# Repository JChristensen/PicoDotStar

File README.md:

# Pico DotStar Driver  
https://github.com/JChristensen/PicoDotstar  
README file  
Jack Christensen  
Apr-2025

## License
  
This work is licensed under the [Creative Commons Attribution-ShareAlike 4.0 International License](https://creativecommons.org/licenses/by-sa/4.0/).

## Overview
This is just a simple carrier board for a Raspberry Pi Pico and an RTC as I begin working with the Pico. I have a couple old projects that use AVR MCUs to drive DotStar LEDs, so replacing those with Picos sounded fairly straightforward. I added a button, three LEDs, and another header with some GPIO pins, so I may also use the board for general experimentation. Once I figure out the Pico's RTC, a separate RTC may not be needed.

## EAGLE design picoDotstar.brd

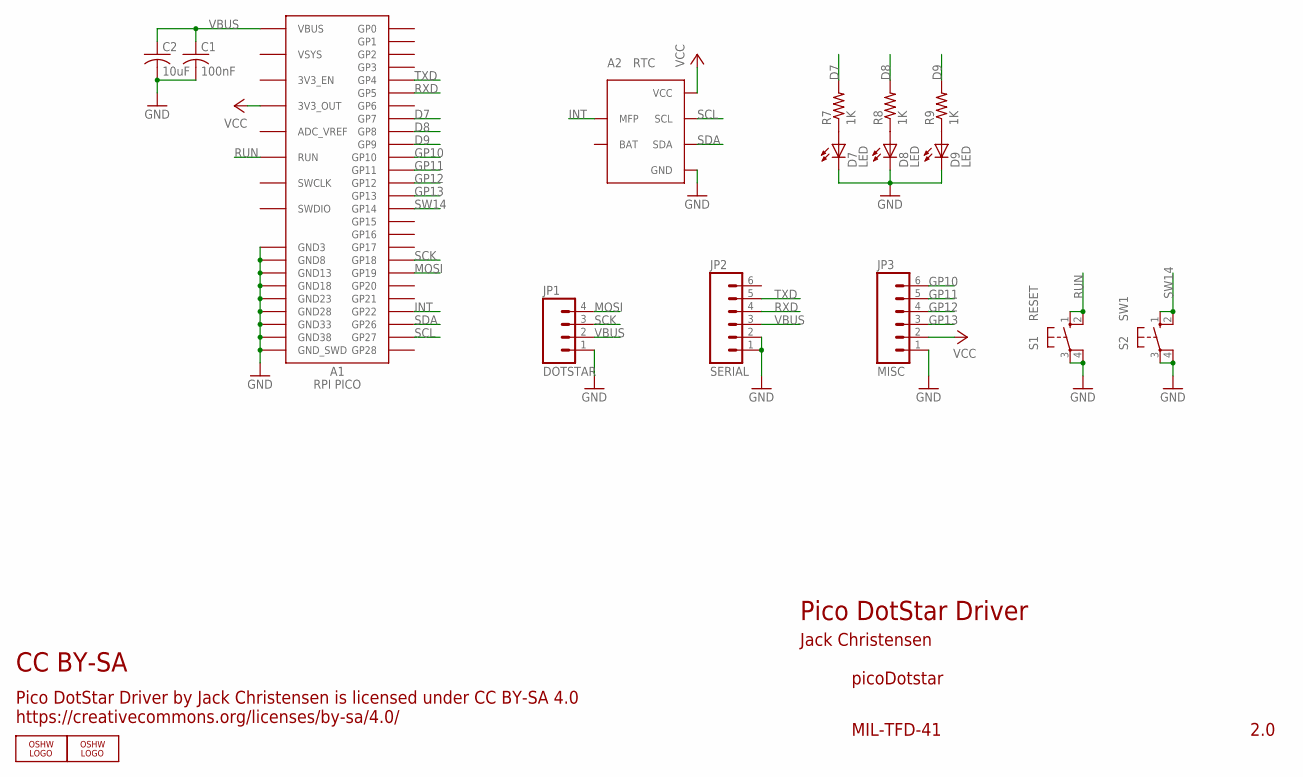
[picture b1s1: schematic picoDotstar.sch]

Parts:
A1: RPI PICO; PICO
A2: RTC; RTC79412
C1: 100nF; M0805
C2: 10uF; M0805
D7, D8, D9: LED; D0805
JP1: DOTSTAR; 1X04_LOCK
JP2: SERIAL; 1X06_LOCK
JP3: MISC; 1X06_LOCK
LOGO2: OSHW_LOGO_8MILX0100-NT; OSHW_8X100_NOTEXT
LOGO3: OSHW_LOGO_8MILX0150-NT; OSHW_8X150_NOTEXT
R7, R8, R9: 1K; M0805
S1: RESET; B3F-10XXOCT
S2: SW1; B3F-10XXOCT

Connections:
D7: A1.P$10 (GP7), R7.2
D8: A1.P$11 (GP8), R8.2
D9: A1.P$12 (GP9), R9.2
GND: A1.P$03 (GND3), A1.P$08 (GND8), A1.P$13 (GND13), A1.P$18 (GND18), A1.P$23 (GND23), A1.P$28 (GND28), A1.P$33 (GND33), A1.P$38 (GND38), A1.P$SWGND (GND_SWD), A2.8 (GND), C1.2, C2.2, D7.K (C), D8.K (C), D9.K (C), JP1.1, JP2.1, JP2.2, JP3.1, S1.3, S1.4 (P1), S2.3, S2.4 (P1)
GP10: A1.P$14 (GP10), JP3.6
GP11: A1.P$15 (GP11), JP3.5
GP12: A1.P$16 (GP12), JP3.4
GP13: A1.P$17 (GP13), JP3.3
INT: A1.P$29 (GP22), A2.3 (MFP)
MOSI: A1.P$25 (GP19), JP1.4
unnamed: D7.A, R7.1
unnamed: D8.A, R8.1
unnamed: D9.A, R9.1
RUN: A1.P$30 (RUN), S1.1 (S), S1.2 (S1)
RXD: A1.P$07 (GP5), JP2.4
SCK: A1.P$24 (GP18), JP1.3
SCL: A1.P$32 (GP27), A2.6 (SCL)
SDA: A1.P$31 (GP26), A2.5 (SDA)
SW14: A1.P$19 (GP14), S2.1 (S), S2.2 (S1)
TXD: A1.P$06 (GP4), JP2.5
VBUS: A1.P$40 (VBUS), C1.1, C2.1, JP1.2, JP2.3
VCC: A1.P$36 (3V3_OUT), A2.7 (VCC), JP3.2

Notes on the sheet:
MIL-TFD-41
Pico DotStar Driver
Jack Christensen
picoDotstar
2.0
CC BY-SA
Pico DotStar Driver by Jack Christensen is licensed under CC BY-SA 4.0 https://creativecommons.org/licenses/by-sa/4.0/

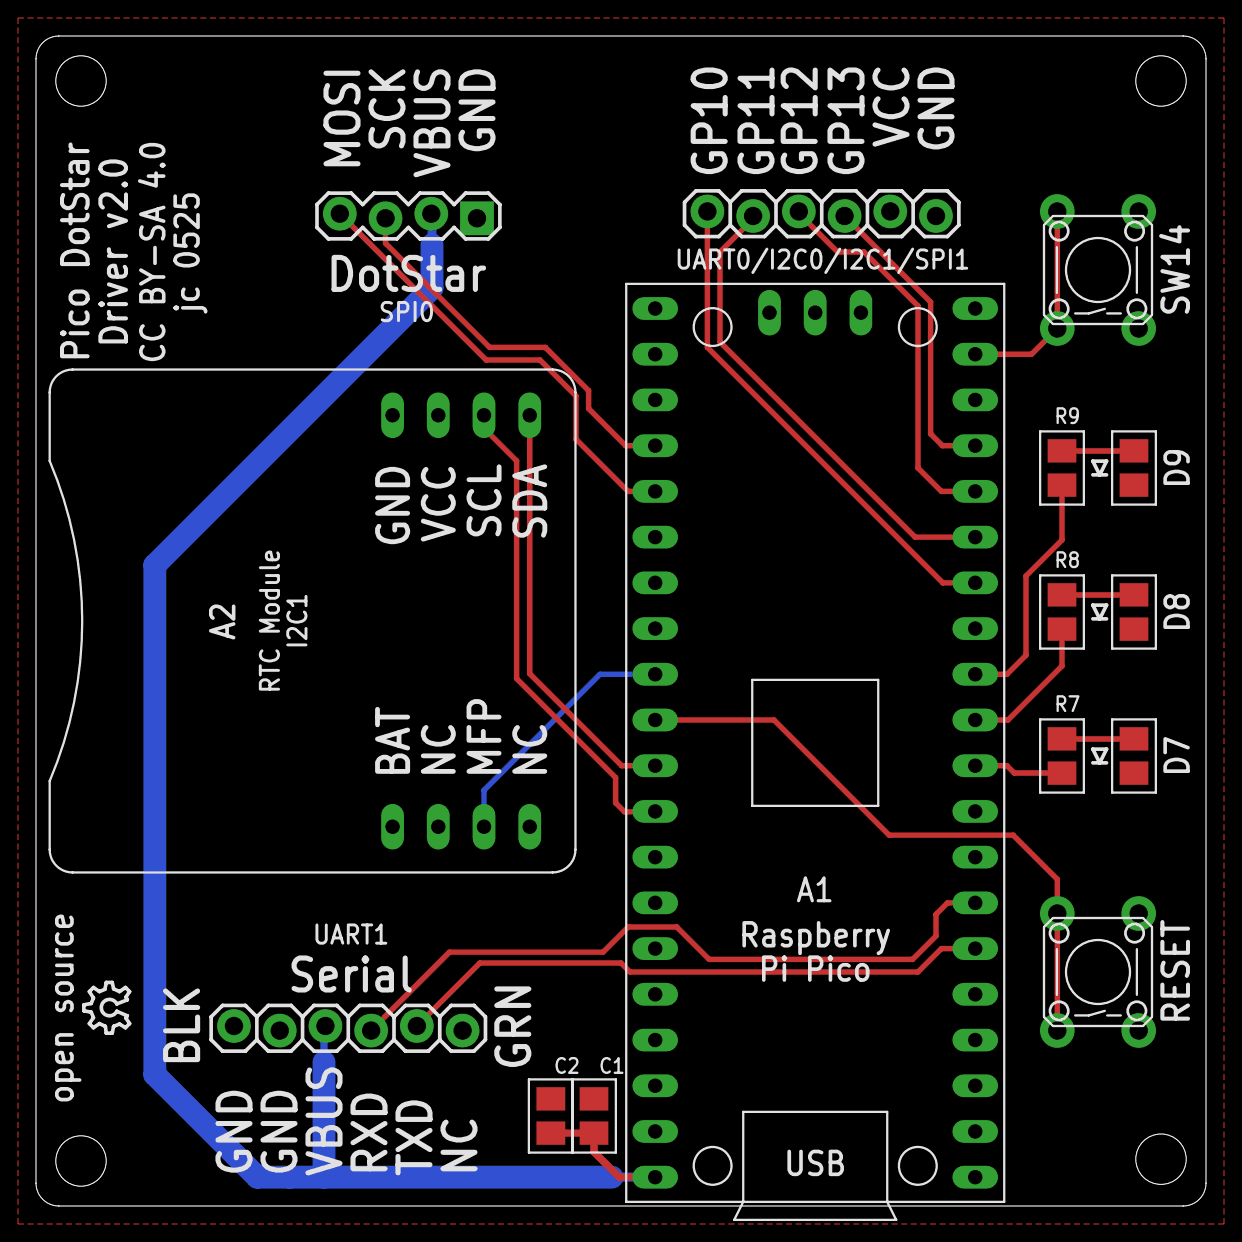
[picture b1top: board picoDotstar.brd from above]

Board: 2 copper layers, 65.0 x 65.0 mm, 17 parts (1 on the bottom side), 22 nets.

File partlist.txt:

Partlist

Exported from picoDotstar.sch at 4/29/25 2:34 PM

EAGLE Version 9.6.2 Copyright (c) 1988-2020 Autodesk, Inc.

Assembly variant: 

Part     Value          Device     Package     Library  Sheet

A1       RPI PICO       PICOPICO   PICO        _jc      1
A2       RTC            RTC79412   RTC79412    _jc      1
C1       100nF          C-USM0805  M0805       _jc      1
C2       10uF           C-USM0805  M0805       _jc      1
D7       LED            LEDD0805   D0805       _jc      1
D8       LED            LEDD0805   D0805       _jc      1
D9       LED            LEDD0805   D0805       _jc      1
JP1      DOTSTAR        M04LOCK    1X04_LOCK   SparkFun 1
JP2      SERIAL         M06LOCK    1X06_LOCK   SparkFun 1
JP3      MISC           M06LOCK    1X06_LOCK   SparkFun 1
R7       1K             R-US_M0805 M0805       _jc      1
R8       1K             R-US_M0805 M0805       _jc      1
R9       1K             R-US_M0805 M0805       _jc      1
S1       RESET          10-XXOCT   B3F-10XXOCT _jc      1
S2       SW1            10-XXOCT   B3F-10XXOCT _jc      1

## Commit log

2025-04-01 Initial commit, v1.0 as sent to fab.
2026-01-28 Move RTC from I2C0 to I2C1.

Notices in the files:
picoDotstar.brd:
CC BY-SA 4.0 jc 0525
parts and their libraries:
SparkFun: Licensing: CC v3.0 Share-Alike You are welcome to use this library for commercial purposes.
